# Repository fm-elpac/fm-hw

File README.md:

<!-- fm-elpac/fm-hw/README.md
  lang: zh_CN
-->

# 胖蚊硬件设计文档
<https://github.com/fm-elpac/fm-hw>

镜像:
+ <https://bitbucket.org/fm-elpac/fm-hw/>
+ <https://codeberg.org/fm-elpac/fm-hw>
+ <https://notabug.org/fm-elpac/fm-hw>
+ <https://gitlab.com/fm-elpac/fm-hw>

**免责声明**: 本项目是开源的项目,
不保证内容的 正确性, 有效性, 安全性.
使用本项目时需要自行评估风险,
并承担使用本项目造成的后果.
本项目默认不适用于儿童.

**商用警告**: 本项目的许可 (CC-BY-SA) 并不禁止商用,
然而本项目不保证不包含专利内容.
商用之前, 需要自行进行专利等合法性评估.

+ 胖蚊战略设计草稿
  <https://github.com/fm-elpac/fm-d>

## 目录

+ **`hw/`**
  硬件设计

## LICENSE

[`CC-BY-SA 4.0+`](https://creativecommons.org/licenses/by-sa/4.0/)

本仓库的内容使用 创意共享-署名-相同方式共享 (CC-BY-SA 4.0) 许可证 (LICENSE).
This repository is released under Creative Common (CC-BY-SA 4.0) license.

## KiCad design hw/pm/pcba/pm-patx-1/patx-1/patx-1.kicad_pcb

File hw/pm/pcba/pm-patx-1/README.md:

# ATX 供电引出板

型号及版本: `pm-patx-1 v0.1`

## 说明

TODO

## 电路板信息

| 参数 | 值 | 备注 |
| :--- | :- | :--- |
| 层数 | 2 | |
| 长宽 | 60mm x 70mm | |
| 板厚 | 1.6mm | |
| 材质 | FR-4 | |
| 铜厚 | 35um (1oz) | |

### 材料清单 (BOM)

| 序号 | 元件 | 封装 | 数量 | 参考价格 (CNY) | 备注 |
| :--: | :--- | :--- | ---: | -------------: | :--- |
| 1 | Molex 5566-24A | 直插 4.2mm 间距 | 1 | 2.35 | ATX 24 针 主板供电接口 |
| 2 | xt60 插座 | 直插 | 2 | 1.36 | |
| 3 | xt30 插座 | 直插 | 2 | 1.19 | |
| 4 | USB-A 插座 (侧插 立式) | 直插 | 4 | 0.53 | |
| 5 | 排针 1x8 | 直插 2.54mm 间距 | 1 | 0.08 | |
| 6 | 排针 2x8 | 直插 2.54mm 间距 | 5 | 0.20 | |
| 7 | MSK-12D19 1P2T | 直插 | 1 | 0.42 | 拨动开关 3 脚 |
| 8 | LED (黄色) | 贴片 0805 | 1 | 0.09 | |
| 9 | 电阻 (200R) | 贴片 0805 | 1 | 0.02 | |
| 总计 | 9 | 8 | 18 | 11.18 | |

成本估算:
PCB 成本 1.25 元, 元件成本 11.18 元 (最大), PCBA 成本 12.5 元 (最大).
最小元件成本 3.28 元 (不焊接所有可选器件), PCBA 最小成本 4.6 元.

## 电路板制造记录

| 序号 | 日期 | 版本 | 厂家 | 测试结果 | 备注 |
| :--: | :--- | :--- | :--- | :------- | :--- |
| 1 | 2024-02-01 | pm-patx-1 v0.1 | JLC | ? | (1) |

注:

+ (1) 阻焊颜色: 黄 (丝印颜色: 白)

TODO

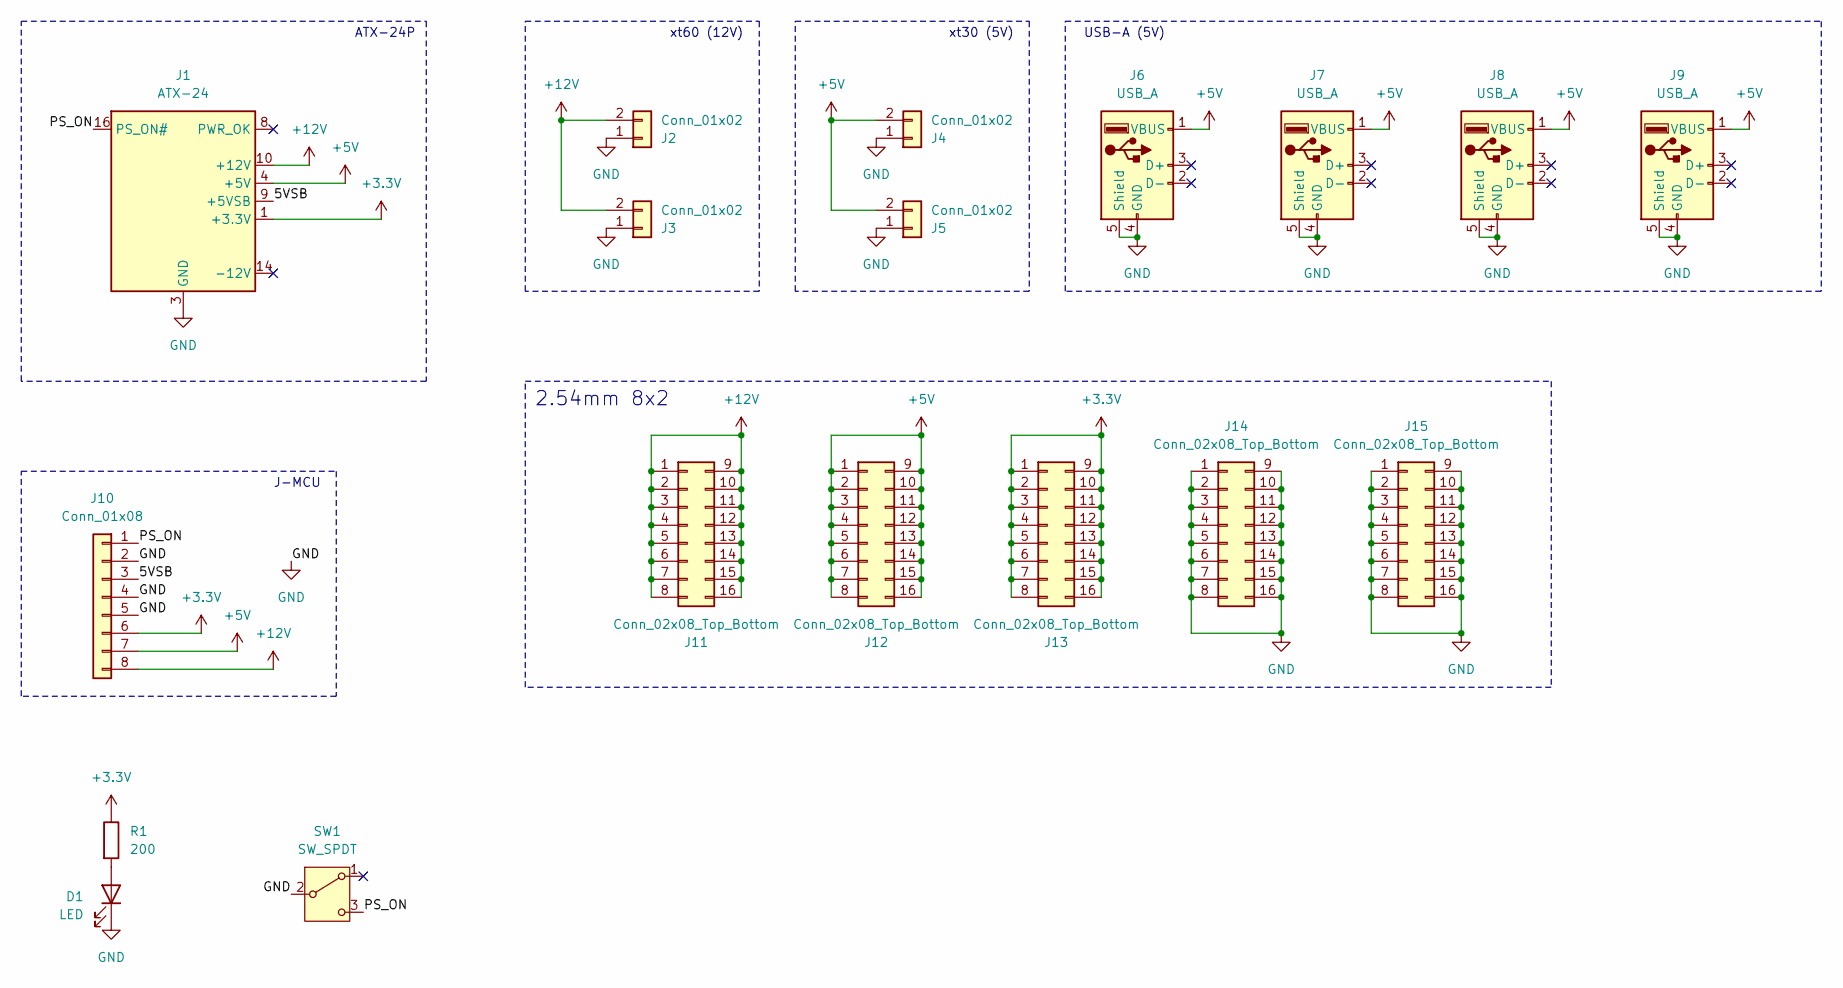
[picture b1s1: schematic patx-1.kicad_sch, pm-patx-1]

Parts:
D1: LED; LED_0805_2012Metric_Pad1.15x1.40mm_HandSolder
J1: ATX-24; Molex_Mini-Fit_Jr_5566-24A_2x12_P4.20mm_Vertical
J2, J3: Conn_01x02; AMASS_XT60-F_1x02_P7.20mm_Vertical
J4, J5: Conn_01x02; AMASS_XT30UPB-F_1x02_P5.0mm_Vertical
J6, J7, J8, J9: USB_A; USB-A-V1
J10: Conn_01x08; PinHeader_1x08_P2.54mm_Vertical
J11, J12, J13, J14, J15: Conn_02x08_Top_Bottom; PinHeader_2x08_P2.54mm_Vertical
R1: 200; R_0805_2012Metric_Pad1.20x1.40mm_HandSolder
SW1: SW_SPDT; MKS-12D19

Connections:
+3.3V: J1.1 (+3.3V), J1.2 (+3.3V), J1.12 (+3.3V), J1.13 (+3.3V), J10.6, J13.1, J13.2, J13.3, J13.4, J13.5, J13.6, J13.7, J13.8, J13.9, J13.10, J13.11, J13.12, J13.13, J13.14, J13.15, J13.16, R1.1
+5V: J1.4 (+5V), J1.6 (+5V), J1.21 (+5V), J1.22 (+5V), J1.23 (+5V), J4.2, J5.2, J6.1 (VBUS), J7.1 (VBUS), J8.1 (VBUS), J9.1 (VBUS), J10.7, J12.1, J12.2, J12.3, J12.4, J12.5, J12.6, J12.7, J12.8, J12.9, J12.10, J12.11, J12.12, J12.13, J12.14, J12.15, J12.16
+12V: J1.10 (+12V), J1.11 (+12V), J2.2, J3.2, J10.8, J11.1, J11.2, J11.3, J11.4, J11.5, J11.6, J11.7, J11.8, J11.9, J11.10, J11.11, J11.12, J11.13, J11.14, J11.15, J11.16
/5VSB: J1.9 (+5VSB), J10.3
/PS_ON: J1.16 (PS_ON#), J10.1, SW1.3 (C)
GND: D1.1 (K), J1.3 (GND), J1.5 (GND), J1.7 (GND), J1.15 (GND), J1.17 (GND), J1.18 (GND), J1.19 (GND), J1.24 (GND), J2.1, J3.1, J4.1, J5.1, J6.4 (GND), J6.5 (Shield), J7.4 (GND), J7.5 (Shield), J8.4 (GND), J8.5 (Shield), J9.4 (GND), J9.5 (Shield), J10.2, J10.4, J10.5, J14.1, J14.2, J14.3, J14.4, J14.5, J14.6, J14.7, J14.8, J14.9, J14.10, J14.11, J14.12, J14.13, J14.14, J14.15, J14.16, J15.1, J15.2, J15.3, J15.4, J15.5, J15.6, J15.7, J15.8, J15.9, J15.10, J15.11, J15.12, J15.13, J15.14, J15.15, J15.16, SW1.2 (B)
unnamed: D1.2 (A), R1.2

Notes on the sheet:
USB-A (5V)
J-MCU
xt30 (5V)
xt60 (12V)
ATX-24P
2.54mm 8x2

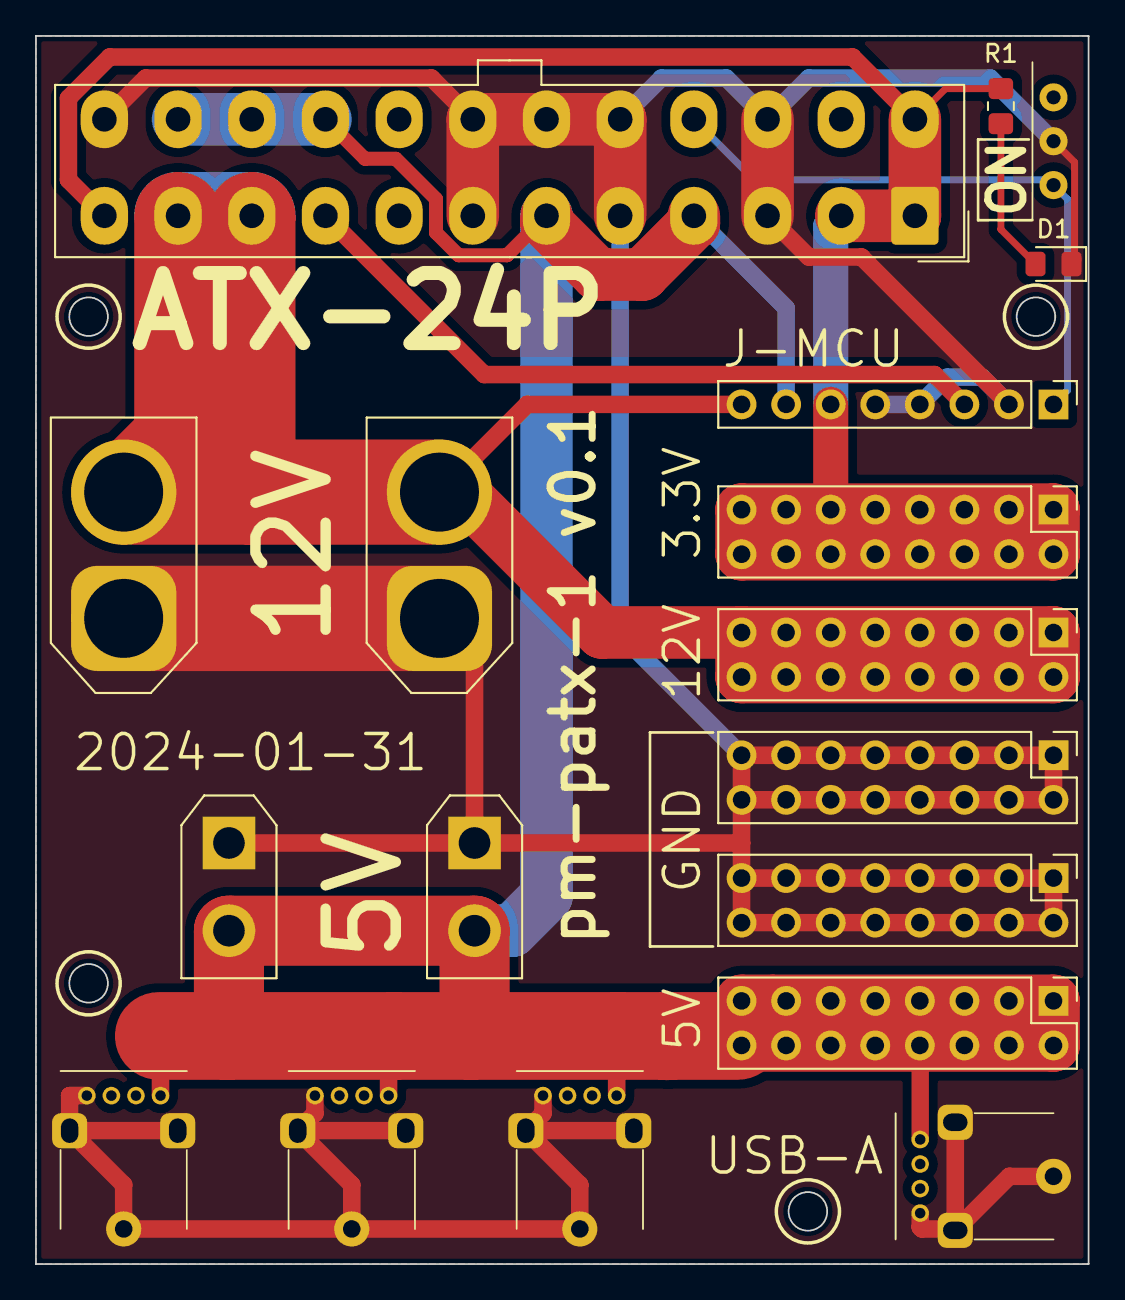
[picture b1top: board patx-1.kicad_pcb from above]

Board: 2 copper layers, 60.0 x 70.0 mm, 18 parts (0 on the bottom side), 7 nets.

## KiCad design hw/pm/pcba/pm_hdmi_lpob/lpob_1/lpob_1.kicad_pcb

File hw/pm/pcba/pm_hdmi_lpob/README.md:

# HDMI 低速引出板

型号及版本: `pm_hdmi_lpob v0.1`

## 说明

HDMI 接口 (A 型) 一共有 19 个引脚 (算上外壳是 20 个),
其中 1 ~ 12 为高速差分信号 (共 12 个, 含信号屏蔽),
本电路板引出其余的低速信号 (共 8 个).

本电路板共有 3 个连接器:
HDMI 插头 (A 型), HDMI 插座 (A 型), 2.54mm 排针 (8 针).
其中 1 ~ 12 高速信号直接通过, 其余 8 个通过排针旁路引出.

本电路板可用于 DDC/CI (i2c), CEC, 调试 (小米电视) 等功能.

## 电路板信息

| 参数 | 值 | 备注 |
| :--- | :- | :--- |
| 层数 | 2 | |
| 长宽 | 48mm x 19mm | |
| 板厚 | 1.6mm | |
| 材质 | FR-4 | |
| 铜厚 | 35um (1oz) | |

### 材料清单 (BOM)

| 序号 | 名称 | 数量 | 参考价格 (CNY) | 备注 |
| :--: | :--- | ---: | -------------: | :--- |
| 1 | HDMI-A 插头夹板 (1.6mm) | 1 | 0.38 | |
| 2 | HDMI-A 插座夹板 (1.6mm) | 1 | 0.42 | |
| 3 | 2.54mm 排针 (1x8) | 1 | 0.08 | |
| 总计 | | 3 | 0.88 | |

+ PCB 成本 (每片): 约 2.5

+ PCBA 成本 (每片): 约 3.4

## HDMI 引脚定义

参考资料:
+ <https://pinoutguide.com/Video/hdmi_pinout.shtml>

HDMI 插头 (A 型):

| 序号 | 名称 | 说明 | 信号类型 | 位置* |
| :--: | :--- | :--- | :------: | :---: |
| 1 | TMDS 数据 2 + | 差分信号 (数据) | 高速 | 1 |
| 2 | TMDS 数据 2 屏蔽 | | 信号屏蔽 | 2 |
| 3 | TMDS 数据 2 - | 差分信号 (数据) | 高速 | 1 |
| 4 | TMDS 数据 1 + | 差分信号 (数据) | 高速 | 2 |
| 5 | TMDS 数据 1 屏蔽 | | 信号屏蔽 | 1 |
| 6 | TMDS 数据 1 - | 差分信号 (数据) | 高速 | 2 |
| 7 | TMDS 数据 0 + | 差分信号 (数据) | 高速 | 1 |
| 8 | TMDS 数据 0 屏蔽 | | 信号屏蔽 | 2 |
| 9 | TMDS 数据 0 - | 差分信号 (数据) | 高速 | 1 |
| 10 | TMDS 时钟 + | 差分信号 (时钟) | 高速 | 2 |
| 11 | TMDS 时钟 屏蔽 | | 信号屏蔽 | 1 |
| 12 | TMDS 时钟 - | 差分信号 (时钟) | 高速 | 2 |
| 13 | CEC | 用于 HDMI CEC 功能 | **低速** | 1 |
| 14 | HEAC+ | (可选) ARC, HEC 等功能 | **低速** | 2 |
| 15 | SCL | 用于 DDC 功能 (i2c) | **低速** | 1 |
| 16 | SDA | 用于 DDC 功能 (i2c) | **低速** | 2 |
| 17 | GND | 接地 (DDC/CEC/HEC) | | 1 |
| 18 | +5V | 电源 (EDID/DDC) | | 2 |
| 19 | HEAC- | (可选) ARC, HEC 等功能 | **低速** | 1 |
| 20 | 接地 | 插头外壳 | | |

注:

+ 位置: `1` 表示在连接器的上方一侧, `2` 表示在连接器的下方一侧.

## 电路板制造记录

| 序号 | 日期 | 版本 | 厂家 | 测试结果 | 备注 |
| :--: | :--- | :--- | :--- | :------- | :--- |
| 1 | 2024-01-03 | pm_hdmi_lpob v0.1 | JLC | 成功 | (1) |

注:

+ (1) 阻焊颜色: 白 (丝印颜色: 黑)

  测试成功: 所有功能符合预期, 工作正常.

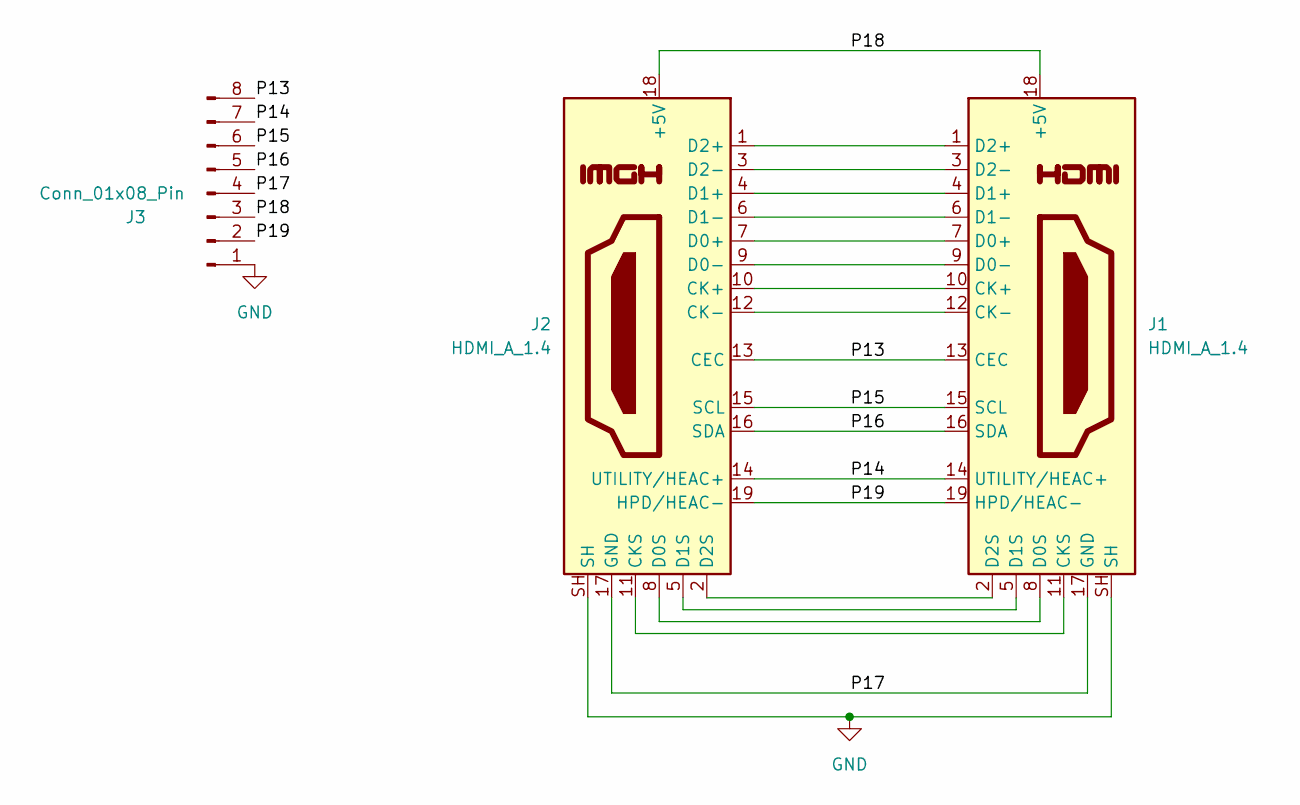
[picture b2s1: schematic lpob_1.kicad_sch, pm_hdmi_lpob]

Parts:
J1: HDMI_A_1.4; hdmi_a_0
J2: HDMI_A_1.4; hdmi_a_1
J3: Conn_01x08_Pin; PinHeader_1x08_P2.54mm_Vertical

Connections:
/P13: J1.13 (CEC), J2.13 (CEC), J3.8
/P14: J1.14 (UTILITY/HEAC+), J2.14 (UTILITY/HEAC+), J3.7
/P15: J1.15 (SCL), J2.15 (SCL), J3.6
/P16: J1.16 (SDA), J2.16 (SDA), J3.5
/P17: J1.17 (GND), J2.17 (GND), J3.4
/P18: J1.18 (+5V), J2.18 (+5V), J3.3
/P19: J1.19 (HPD/HEAC-), J2.19 (HPD/HEAC-), J3.2
GND: J1.SH, J2.SH, J3.1
unnamed: J1.10 (CK+), J2.10 (CK+)
unnamed: J1.12 (CK-), J2.12 (CK-)
unnamed: J1.11 (CKS), J2.11 (CKS)
unnamed: J1.7 (D0+), J2.7 (D0+)
unnamed: J1.9 (D0-), J2.9 (D0-)
unnamed: J1.8 (D0S), J2.8 (D0S)
unnamed: J1.4 (D1+), J2.4 (D1+)
unnamed: J1.6 (D1-), J2.6 (D1-)
unnamed: J1.5 (D1S), J2.5 (D1S)
unnamed: J1.1 (D2+), J2.1 (D2+)
unnamed: J1.3 (D2-), J2.3 (D2-)
unnamed: J1.2 (D2S), J2.2 (D2S)

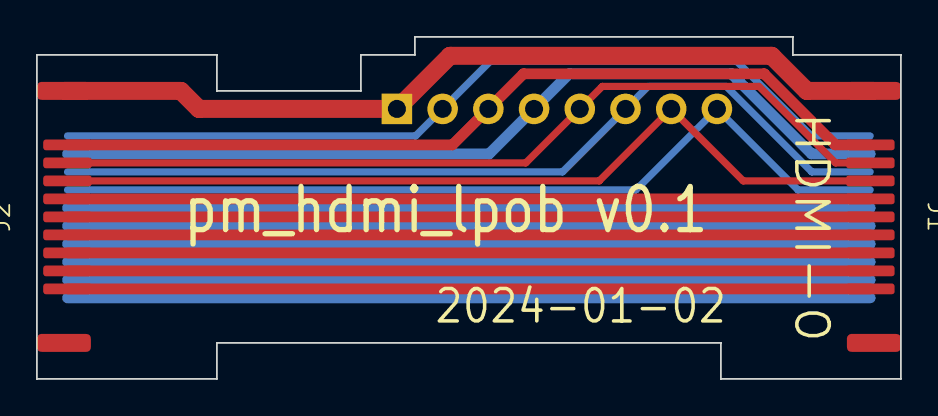
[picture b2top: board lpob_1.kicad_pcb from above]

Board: 2 copper layers, 48.0 x 19.0 mm, 3 parts (1 on the bottom side), 20 nets.

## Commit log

2022-06-12 首次提交
2024-01-01 重置 git 历史
2024-01-01 添加(pm/pcba): pm_hdmi_lpob
2024-01-03 添加(pm/pcba): 生产 PCB JLC pm_hdmi_lpob v0.1 (2024-01-03)
2024-01-03 添加(pm/pcba): pm_hdmi_lpob 材料清单
2024-01-10 添加(pm/pcba): pm_hdmi_lpob 测试成功
2024-01-18 添加(pm/pcba): pmtd-1/t1
2024-01-29 添加(草稿): pm/pcba: pm-patx-1
2024-01-29 添加(pm/pcba): pm-patx-1
2024-02-01 添加(pm/pcba): 打样 pm-patx-1
